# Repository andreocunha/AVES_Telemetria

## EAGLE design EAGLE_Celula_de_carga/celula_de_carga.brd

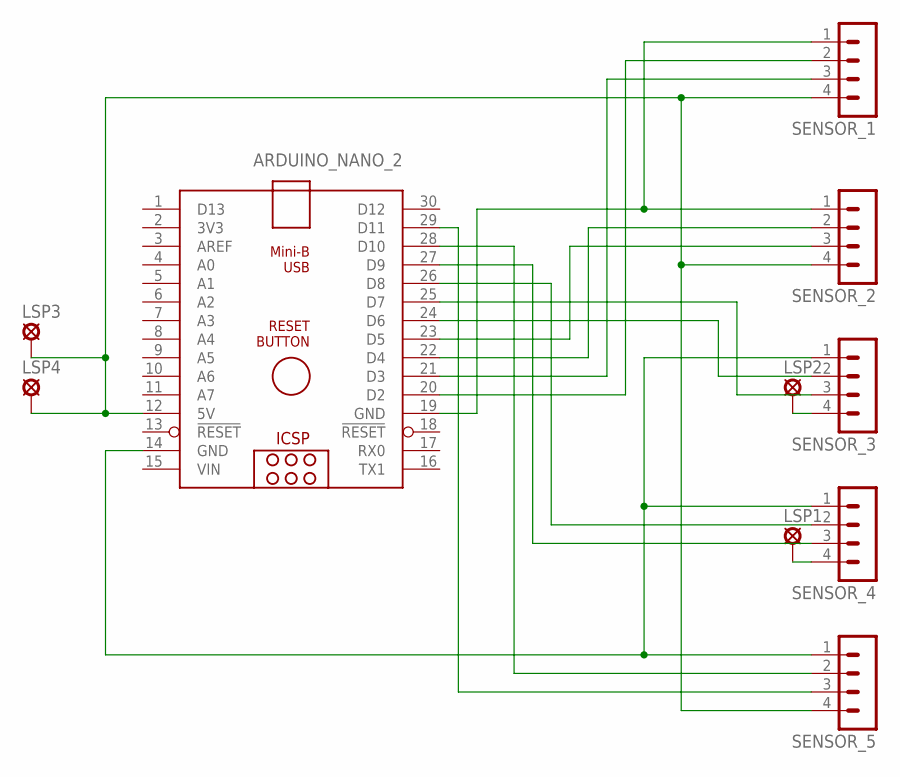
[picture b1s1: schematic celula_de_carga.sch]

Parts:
ARDUINO_NANO_2: ARDUINO_NANO
LSP1, LSP2, LSP3, LSP4: LSP10
SENSOR_1, SENSOR_2, SENSOR_3, SENSOR_4, SENSOR_5: MA04-1

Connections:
unnamed: ARDUINO_NANO_2.14 (GND), SENSOR_3.1, SENSOR_4.1, SENSOR_5.1
unnamed: ARDUINO_NANO_2.19 (GND), SENSOR_1.1, SENSOR_2.1
unnamed: ARDUINO_NANO_2.28 (D10), SENSOR_5.2
unnamed: ARDUINO_NANO_2.20 (D2), SENSOR_1.2
unnamed: ARDUINO_NANO_2.21 (D3), SENSOR_1.3
unnamed: ARDUINO_NANO_2.22 (D4), SENSOR_2.2
unnamed: ARDUINO_NANO_2.23 (D5), SENSOR_2.3
unnamed: ARDUINO_NANO_2.24 (D6), SENSOR_3.2
unnamed: ARDUINO_NANO_2.25 (D7), SENSOR_3.3
unnamed: ARDUINO_NANO_2.26 (D8), SENSOR_4.2
unnamed: ARDUINO_NANO_2.27 (D9), SENSOR_4.3
unnamed: ARDUINO_NANO_2.29 (D11), SENSOR_5.3
unnamed: LSP1.MP, SENSOR_4.4
unnamed: ARDUINO_NANO_2.12 (5V), LSP3.MP, LSP4.MP, SENSOR_1.4, SENSOR_2.4, SENSOR_5.4
unnamed: LSP2.MP, SENSOR_3.4
VIN: ARDUINO_NANO_2.15 (VIN)

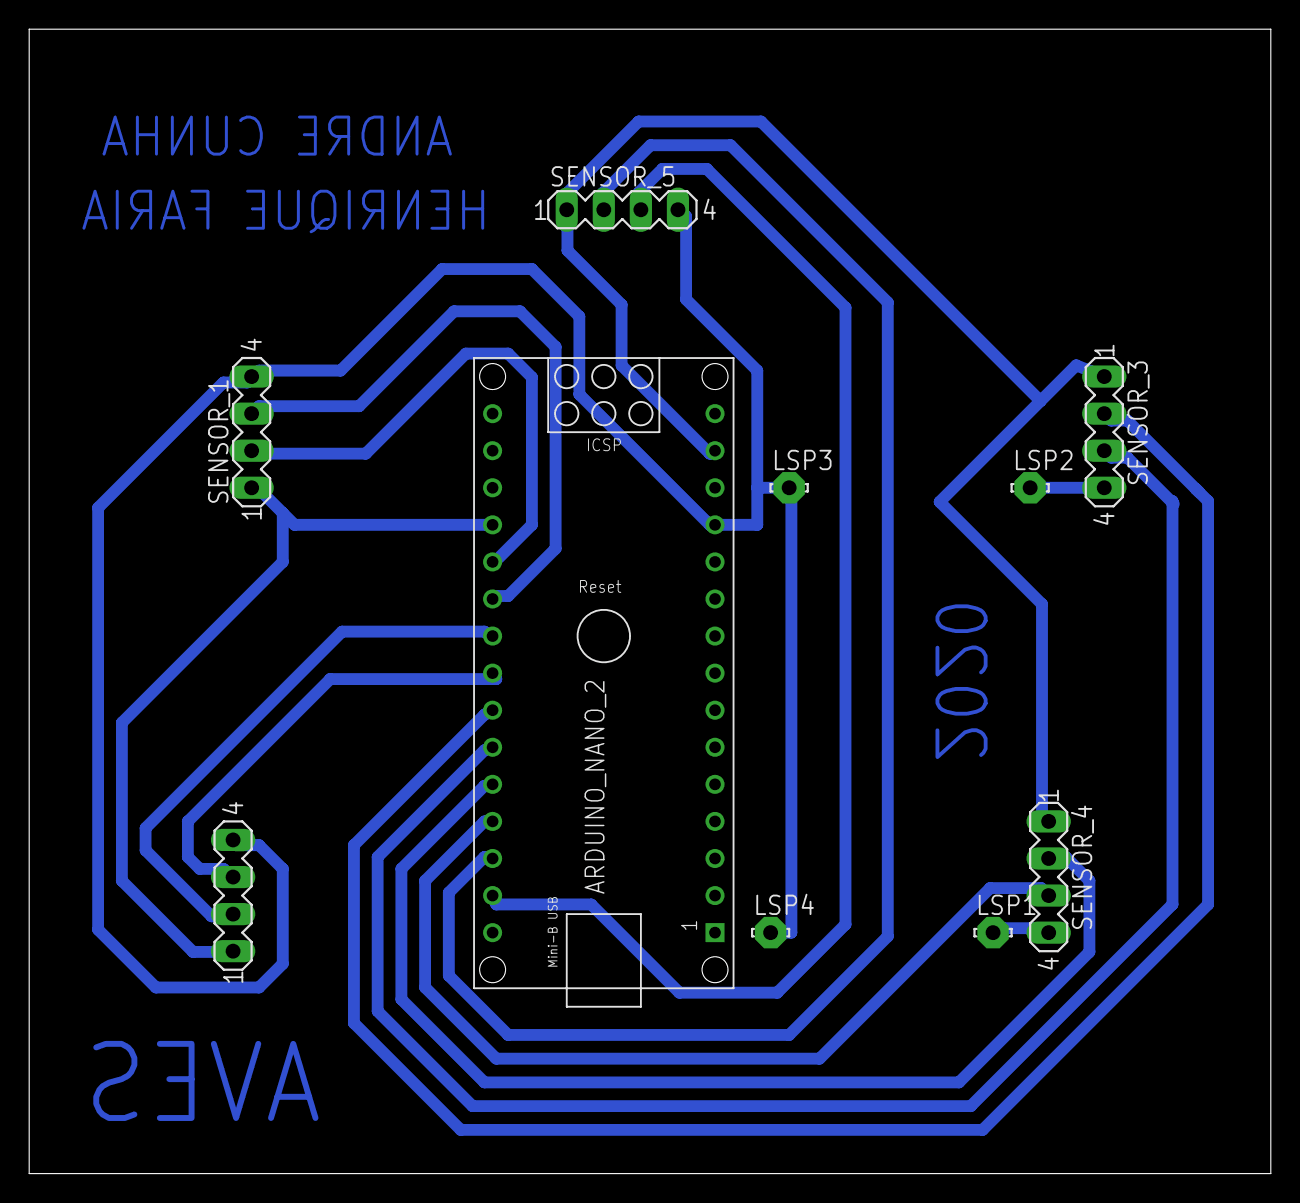
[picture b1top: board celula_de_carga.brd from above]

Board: 2 copper layers, 85.1 x 78.4 mm, 10 parts (0 on the bottom side), 15 nets.

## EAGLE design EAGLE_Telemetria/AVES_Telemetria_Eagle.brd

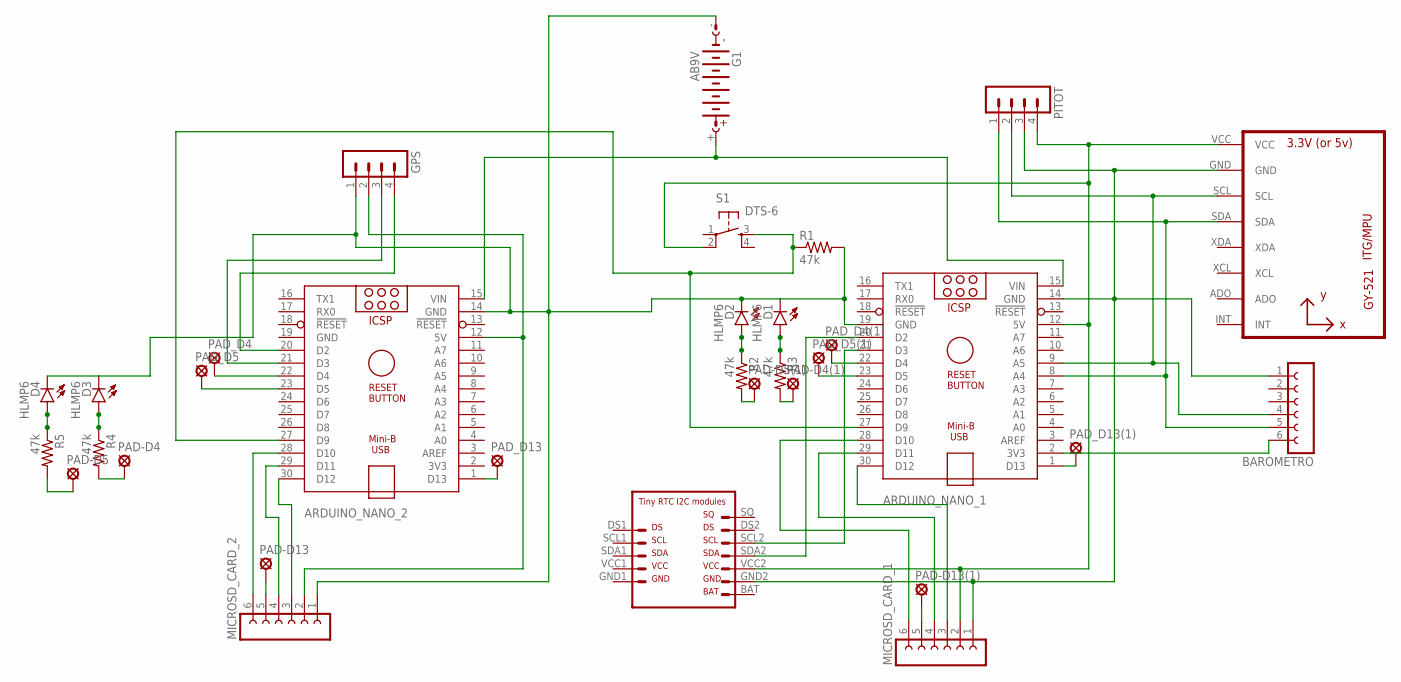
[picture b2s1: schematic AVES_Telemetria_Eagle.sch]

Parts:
ARDUINO_NANO_1, ARDUINO_NANO_2: ARDUINO_NANO
BAROMETRO: FE06-1; FE06
D1, D2, D3, D4: HLMP6
G1: AB9V
GPS: MA04-1
MICROSD_CARD_1, MICROSD_CARD_2: FE06-1; FE06
PAD-D4, PAD-D4(1), PAD-D5, PAD-D5(1), PAD-D13, PAD-D13(1): LSP10
PAD_D4, PAD_D4(1), PAD_D5, PAD_D5(1), PAD_D13, PAD_D13(1): LSP10
PITOT: MA04-1
R1, R2, R3, R4, R5: 47k; 0204/5
S1: DTS-6
U1: GY-521MPU6050; GY-521
U$1: RTC

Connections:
GND: ARDUINO_NANO_2.19 (GND)
unnamed: D1.A, R3.1
unnamed: PAD-D4(1).MP, R3.2
unnamed: D2.A, R2.1
unnamed: ARDUINO_NANO_1.23 (D5), PAD_D5(1).MP
unnamed: ARDUINO_NANO_1.27 (D9), ARDUINO_NANO_2.27 (D9), R1.1, S1.3
unnamed: ARDUINO_NANO_1.12 (5V), MICROSD_CARD_1.2, PITOT.4, S1.2, U1.VCC, U$1.VCC2
unnamed: ARDUINO_NANO_1.15 (VIN), ARDUINO_NANO_2.15 (VIN), G1.+
unnamed: ARDUINO_NANO_1.20 (D2), U$1.SDA2
unnamed: ARDUINO_NANO_1.21 (D3), U$1.SCL2
unnamed: ARDUINO_NANO_1.8 (A4), BAROMETRO.5, PITOT.1, U1.SDA
unnamed: ARDUINO_NANO_1.9 (A5), BAROMETRO.4, PITOT.2, U1.SCL
unnamed: ARDUINO_NANO_1.2 (3V3), BAROMETRO.6
unnamed: ARDUINO_NANO_1.28 (D10), MICROSD_CARD_1.6
unnamed: MICROSD_CARD_1.5, PAD-D13(1).MP
unnamed: ARDUINO_NANO_1.29 (D11), MICROSD_CARD_1.4
unnamed: ARDUINO_NANO_1.30 (D12), MICROSD_CARD_1.3
unnamed: ARDUINO_NANO_1.19 (GND), ARDUINO_NANO_2.14 (GND), D1.K, D2.K, D3.K, D4.K, G1.-, GPS.1, MICROSD_CARD_2.1, R1.2
unnamed: ARDUINO_NANO_2.12 (5V), GPS.2, MICROSD_CARD_2.2
unnamed: ARDUINO_NANO_2.21 (D3), GPS.3
unnamed: ARDUINO_NANO_2.20 (D2), GPS.4
unnamed: PAD-D4.MP, R4.2
unnamed: ARDUINO_NANO_2.22 (D4), PAD_D4.MP
unnamed: ARDUINO_NANO_2.30 (D12), MICROSD_CARD_2.3
unnamed: ARDUINO_NANO_2.29 (D11), MICROSD_CARD_2.4
unnamed: MICROSD_CARD_2.5, PAD-D13.MP
unnamed: ARDUINO_NANO_2.28 (D10), MICROSD_CARD_2.6
unnamed: ARDUINO_NANO_2.23 (D5), PAD_D5.MP
unnamed: D3.A, R4.1
unnamed: PAD-D5.MP, R5.2
unnamed: D4.A, R5.1
unnamed: ARDUINO_NANO_1.22 (D4), PAD_D4(1).MP
unnamed: PAD-D5(1).MP, R2.2
unnamed: ARDUINO_NANO_2.1 (D13), PAD_D13.MP
unnamed: ARDUINO_NANO_1.1 (D13), PAD_D13(1).MP
unnamed: ARDUINO_NANO_1.14 (GND), BAROMETRO.1, MICROSD_CARD_1.1, PITOT.3, U1.GND, U$1.GND2

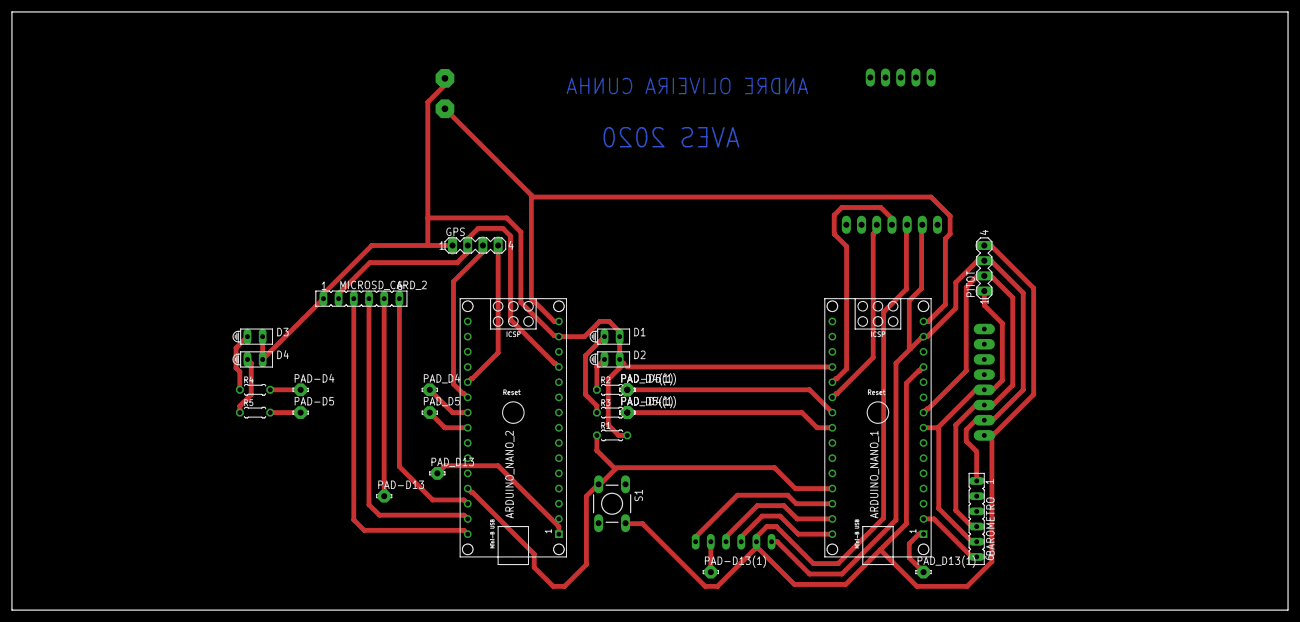
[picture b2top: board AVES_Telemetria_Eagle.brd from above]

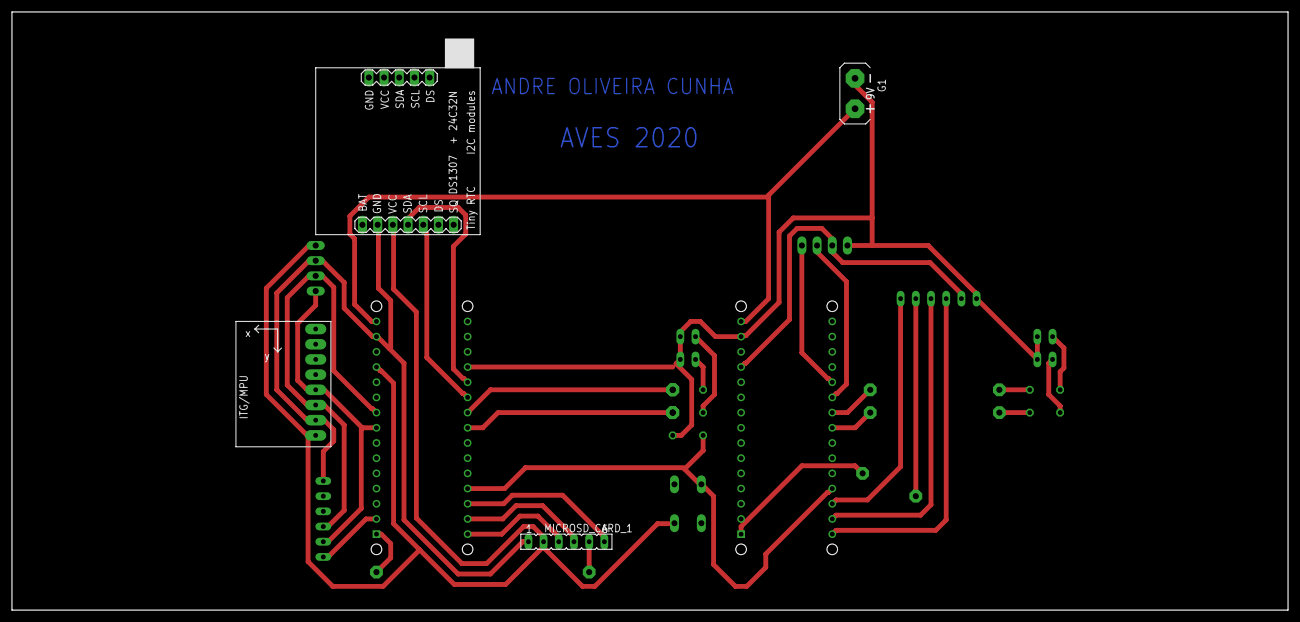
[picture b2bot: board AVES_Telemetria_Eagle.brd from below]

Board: 2 copper layers, 213.3 x 100.0 mm, 32 parts (4 on the bottom side), 35 nets.
